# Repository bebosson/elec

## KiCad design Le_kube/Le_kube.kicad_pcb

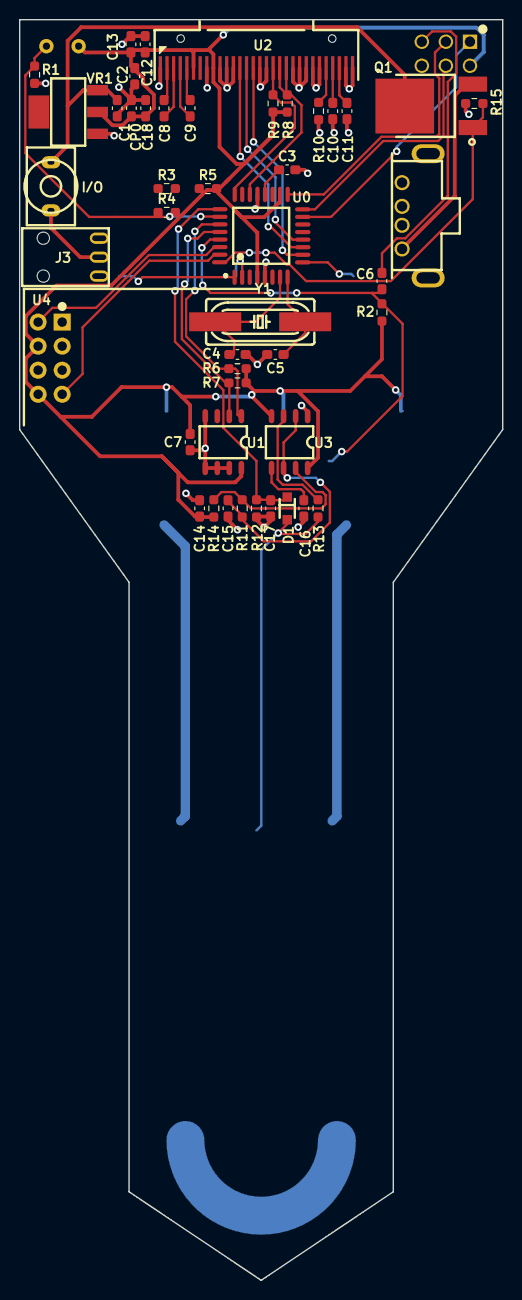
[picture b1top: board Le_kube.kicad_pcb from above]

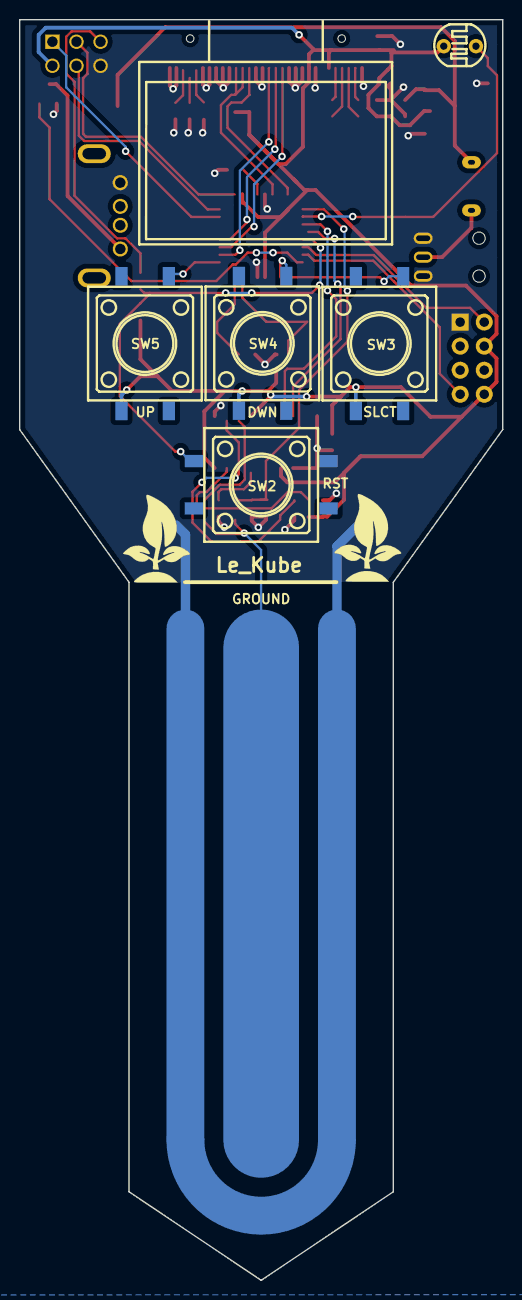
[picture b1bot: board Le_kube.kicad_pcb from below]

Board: 2 copper layers, 51.0 x 133.1 mm, 53 parts (6 on the bottom side), 40 nets.

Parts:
C1, C3, C6, C7, C14, C18: 100nF; C_0603_1608Metric_Pad1.08x0.95mm_HandSolder
C2: 10µF; C_0603_1608Metric_Pad1.08x0.95mm_HandSolder
C4, C5: 30pF; C_0603_1608Metric_Pad1.08x0.95mm_HandSolder
C8, C9, C12, C13, C17: 1µF; C_0603_1608Metric_Pad1.08x0.95mm_HandSolder
C10: 4.7µF; C_0603_1608Metric_Pad1.08x0.95mm_HandSolder
C11: 2.2µF; C_0603_1608Metric_Pad1.08x0.95mm_HandSolder
C15: 470pF; C_0603_1608Metric_Pad1.08x0.95mm_HandSolder
C16: 10nF; C_0603_1608Metric_Pad1.08x0.95mm_HandSolder
C19: GROUND; PROBE
CP0: 10µF; C_0603_1608Metric_Pad1.08x0.95mm_HandSolder
D1: D; SOD-323_L1.8-W1.3-LS2.5-RD
I O: I/O; SW-TH_L8.0-W5.11-P5.08_TP11SH8CQE
J1: Conn_01x06_Male; AVR-ISP(IDC-TH_6P-P2.54_C11214)
J2: USB_A; USB-A-TH_USB-302-T
J3: Barrel_Jack_Switch; PORT-JACK(DC-IN-TH_DC-003-2A-1.3)
LDR1: LDR; LDR(RES-TH_L5.1-W4.3-P3.40-D0.5)
Q1: IRLB8721PBF; MOSFET(DPAK_L6.5-W6.0-P2.29-LS9.9-BR)
R1, R2, R3, R4, R5, R6, R7, R13, R15: 10K; R_0603_1608Metric_Pad0.98x0.95mm_HandSolder
R8, R9: 4.7K; R_0603_1608Metric_Pad0.98x0.95mm_HandSolder
R10: 910K; R_0603_1608Metric_Pad0.98x0.95mm_HandSolder
R11: 1.6K; R_0603_1608Metric_Pad0.98x0.95mm_HandSolder
R12: 1M; R_0603_1608Metric_Pad0.98x0.95mm_HandSolder
R14: 330R; R_0603_1608Metric_Pad0.98x0.95mm_HandSolder
SW2: RST; KEY-SMD_4P-L12.0-W12.0-P5.00-LS15.2
SW3, SW4, SW5: SW_Push; KEY-SMD_4P-L12.0-W12.0-P5.00-LS15.2
U0: ATmega328PB-AU; ATMEGA328PB-AU(TQFP-32_L7.0-W7.0-P0.80-LS9.0-BL)
U1: LM75A; TEMP_SENSOR(SOIC-8_L5.0-W4.0-P1.27-LS6.0-BL)
U2: 128x64_OLED; OLED-0.96-12864
U3: TLC555CDR; TLC555(SOIC-8_L5.0-W4.0-P1.27-LS6.0-BL)
U4: ESP8266-01_ESP-01; ESP-01S(WIFIM-TH_8P-L24.7-W14.4-P2.54)
VR1: LD1117; LD1117(SOT-223_L6.7-W3.5-P2.30-BR)
Y1: Crystal; Crystal(HC-49S_L11.4-W4.8)

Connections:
+3V3: C2.1, C7.2, C12.1, C13.1, C14.2, C18.1, CP0.1, J1.2, LDR1.2, R2.1, R6.1, R7.2, R8.2, R9.2, R14.2, SW3.2, SW4.2, SW5.2, U0.4, U0.18, U1.8, U2.6, U2.9, U3.4, U3.8, U4.6, U4.8, VR1.2
+5V: I O.1, J3.2
/ESP_RX: U0.31, U4.4
/ESP_TX: U0.30, U4.5
/HUM: C17.2, D1.1, R12.2, U0.25
/ISP_MISO: J1.1, U0.15
/ISP_MOSI: J1.4, U0.16
/ISP_SCK: J1.3, U0.17
/SCL: R7.1, U0.28, U1.2
/SCREEN_MISO: R8.1, U0.22, U2.19, U2.20
/SCREEN_MOSI: U0.10, U2.15
/SCREEN_RST: U0.12, U2.14
/SCREEN_SCK: R9.1, U0.24, U2.18
/SCREEN_SS: U0.11, U2.13
/SDA: R6.2, U0.27, U1.1
/connecteur_isp/RST: C6.1, J1.5
GND: C1.1, C2.2, C3.2, C4.1, C5.1, C7.1, C10.1, C11.1, C12.2, C13.2, C14.1, C15.1, C16.2, C17.1, C18.2, C19.1, CP0.2, J1.6, J2.4, J3.1, J3.3, R1.1, R3.1, R4.1, R5.1, R10.2, R12.1, R15.1, SW2.2, U0.5, U0.21, U1.4, U1.5, U1.6, U1.7, U2.1, U2.8, U2.10, U2.11, U2.12, U2.16, U2.17, U2.21, U2.22, U2.23, U2.24, U2.25, U2.29, U2.30, U3.1, U4.1, VR1.1
unnamed: C1.2, I O.2, Q1.4, VR1.3
unnamed: C3.1, U0.20
unnamed: C4.2, U0.7, Y1.1
unnamed: C5.2, U0.8, Y1.2
unnamed: C6.2, R2.2, SW2.1, U0.29
unnamed: C8.1, U2.2
unnamed: C8.2, U2.3
unnamed: C9.1, U2.4
unnamed: C9.2, U2.5
unnamed: C10.2, U2.27
unnamed: C11.2, U2.28
unnamed: C15.2, R11.1, U3.2, U3.6
unnamed: C16.1, U3.5
unnamed: C19.2, D1.2, R13.1
unnamed: J2.1, Q1.3
unnamed: LDR1.1, R1.2, U0.26
unnamed: Q1.1, R15.2, U0.32
unnamed: R3.2, SW3.1, U0.1
unnamed: R4.2, SW4.1, U0.2
unnamed: R5.2, SW5.1, U0.9
unnamed: R10.1, U2.26
unnamed: R11.2, R14.1, U3.7
unnamed: R13.2, U3.3

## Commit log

2020-10-26 first_commit
2020-10-28 toto
2020-11-09 first_push
2020-11-19 Tpinterrupt
2021-03-01 first_push_final_project
2021-03-10 damn repartition des taches
2021-03-10 hardware serial
2021-03-12 adafruit -> spi_begin_transaction
2021-03-19 custom i2c
2021-03-19 custom i2c end
2021-03-19 i2c goes on
2021-03-22 i2c start working
2021-03-22 i2c works
2021-03-22 removing useless stuff
2021-03-24 gros push pour maison
2021-03-26 custom_screen
2021-03-26 temperature done bitch
2021-03-30 firmware presque fini, manque wifi et la pompe, start cao
2021-04-02 go cao
2021-04-02 pretty
2021-04-05 continue on kicad_ssd1306
2021-04-05 test merge
2021-04-06 screen done
2021-04-08 SWIMMING POULE
2021-04-13 sheet finish ?
2021-04-14 fin de la schematic
2021-04-16 modif atmega328pb
2021-04-16 connector jack DC add
2021-04-16 corrections
2021-04-16 footprint
2021-04-19 footprints done
2021-04-21 read_lux ok
2021-04-22 ca marche le sensor de couilles
2021-04-22 debut routage
2021-04-22 Routage
2021-04-23 routage en cours
2021-04-23 debut du routage (commit de secours)
2021-04-23 conflit ?
2021-04-25 routage done
2021-04-25 routage update
2021-04-26 routage done 2
2021-04-26 routage done 3
2021-04-26 routage done 4
2021-04-26 gerber
2021-05-17 EEPROM requete http
2021-05-21 premier commit app, front + back sur la raspberry, sql fonctionne avec format (date + humidite + luminosite + temperature) qu on remplit sur le front... objectif, empacter les requetes http de lesp p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
2021-05-21 import bdd to front from back :) go to recharts now
2021-05-28 POST Http Request done
2021-05-28 avancee dans automatisation requete POST et son contenu
2021-06-04 last push before esp
2021-06-04 only esp TX
2021-06-08 for the win
2021-06-08 tarte a macron
2021-06-09 clean up
2021-06-09 cleanup
2021-06-09 C T MOI
2021-06-09 Pump
2021-06-09 push last day
2021-06-09 final push inshallah
2021-06-10 last
2021-06-10 last last
2021-06-10 last 2
2021-06-10 last last 2
